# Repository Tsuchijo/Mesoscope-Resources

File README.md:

# TM-Lab-Mesoscope-Resources

## Arduino Code
Installing Arduino IDE:

    Download Arduino IDE:
        Visit the official Arduino website: Arduino Software.
        Choose the appropriate version for your operating system (Windows, macOS, Linux), and download the installer.

    Install Arduino IDE:
        Run the downloaded installer and follow the on-screen instructions.
        On Windows, you might need to install drivers for the Arduino board during the installation process.

    Open Arduino IDE:
        Once installed, open the Arduino IDE.

Installing and Running a Supplied Program:

    Connect Arduino Board:
        Connect your Arduino board to your computer using a USB cable.

    Select Board and Port:
        In the Arduino IDE, go to Tools > Board and select the appropriate Arduino board (e.g., Arduino Uno).
        Also, go to Tools > Port and select the port to which your Arduino board is connected.

    Open a Supplied Program (Sketch):
        Download the sketch from TriggeringstrobingArduinoCode/
        In the Arduino IDE, go to File > open and open the downloaded sketch

    Verify the Sketch:
        Click the checkmark icon (Verify) to check for any errors in the code. Fix any errors if they occur.

    Upload the Sketch:
        Click the right arrow icon (Upload) to compile and upload the sketch to the Arduino board.

## Lens Adapters

All the lens adapters are parametrically created using this onshape file:

https://cad.onshape.com/documents/2f0def30531779d17ee9e510/w/bf5702dd5ef345ce03ccb7df/e/dbd37cfbbbade1fbfb717a2f?renderMode=0&uiState=656536ea70c36e66cdf41a41

Adjust these parameters to change the adapters parameters, the diameter is the inner diameter of the lens, pitch is usually 0.5 or 0.75

## Strobing Trigger

### Circuit Diagrams

### Triggering Unit 

### Routing 

### I/O

For the Master Clock in / power in pin out from left to right is 
- master clock
- ground
- power (5v)

for Timing signal the pinout is
- Brain timing control
- Behavior timing control
- Strobing timing control

with the switches controlling in the same order.

In order to control the width of the timing signal supply a pwm signal to each of the width control signals, with the width corresponding to change in signal. The supplied signal should be greater than 1khz and ideally as high frequency as possible to reduce artifacts

the timing and output pots allow for manual control of timing and output voltage, although each of them can cause errors if pushed to their limits due to variation in their ranges from manufacturing. Never turn the timing pots all the way to the right as that might cause a short

### Using

To use supply a 50hz PWM signal to the master clock with as wide a PWM as possible, the width of the signal corresponding to the maximum possible exposure time.

Supply a 5khz PWM signal for each width control pin in to control the exposure for brain and the behaviour cameras independently. Make sure the switch is switched to ON for the control pin being used. The Width of the PWM signal corresponds with the timing, with the widest signal being the longest exposure time.

Simulation of the circuit can be found at: https://tinyurl.com/ykhpxhtl

### Control Example Code
```import RPi.GPIO as GPIO
import time

# Set GPIO mode and warning
GPIO.setmode(GPIO.BCM)
GPIO.setwarnings(False)

# Define the pin numbers
master_clock_pin = 17
width_control_pin = 18

# Set the frequency for the master clock (50Hz)
master_clock_frequency = 50

# Set the duty cycle for the master clock (99% width)
master_clock_duty_cycle = 99

# Set the frequency for the width control (5kHz)
width_control_frequency = 5000

# Initialize the GPIO pins
GPIO.setup(master_clock_pin, GPIO.OUT)
GPIO.setup(width_control_pin, GPIO.OUT)

# Initialize PWM for master clock
master_clock_pwm = GPIO.PWM(master_clock_pin, master_clock_frequency)
master_clock_pwm.start(master_clock_duty_cycle)

# Function to control the width of the second PWM
def set_width(shutter_speed):
    width_percentage = shutter_speed * 100
    width_control_pwm.ChangeDutyCycle(width_percentage)

# Initialize PWM for width control
width_control_pwm = GPIO.PWM(width_control_pin, width_control_frequency)
width_control_pwm.start(0)  # Start with 0% duty cycle

try:
    # Example: Set shutter speed to 0.5 (50% duty cycle)
    shutter_speed = 0.5
    set_width(shutter_speed)

    # Keep the program running
    while True:
        time.sleep(1)

except KeyboardInterrupt:
    # Clean up on program exit
    master_clock_pwm.stop()
    width_control_pwm.stop()
    GPIO.cleanup()
```

# Throughole Based Triggering System
For making the throughhole 555 trigger there is a .xlsx file with the digikey order needed to create one system. The list can also be found at this link: https://www.digikey.ca/en/mylists/list/3F61W3LRA3. Then the components can be placed on the board based on the silkscreen.

## Circuit Drawing

# Solenoid Driver

The Driver is based on using M7 Mosfet drivers, which max out at ~300 mA of current draw at 12V, anything higher will damage and burn out the driver over time. Not suitable for high power solenoids.

## Circuit Drawing

# Glass Slide Cutting Jigs
https://cad.onshape.com/documents/586ecae177d828403c2f23cb/w/295fcf84d2d2bd0672364755/e/c55ac1745cc839e1a44f1998?renderMode=0&uiState=657b82dfe9d1321263616ee4

the Glass Slide Cutting Jig is parameterized by a variable table which determines the depth of the first and second cuts, made to cut 8mm diameter glass slides, should be 3d printed on fine print settings.

# Columbia Mouse Cup Clear Sides Model
https://cad.onshape.com/documents/b81ce74945475cb4a4585191/w/58aa1f17095117351b4c242d/e/5ae7ff2c3d7fb6816ba1f3a7?renderMode=0&uiState=657b8323ea32e231b383538c

Clear Sided mouse cup for water reaching task. The sides should be laser cut out of 3mm acrylic, the main cup 3d printed.

# Headfix Mount
https://cad.onshape.com/documents/1d2096fc56ebea0ce0825b22/w/af5d367c825ef3549394acac/e/f6e60455f61b46eaad854045?renderMode=0&uiState=657b836199fdb972703cfb45

Model and Drawing for headfix mount, should be tapped and machined. Used JLCPCB to order the Machined versions.

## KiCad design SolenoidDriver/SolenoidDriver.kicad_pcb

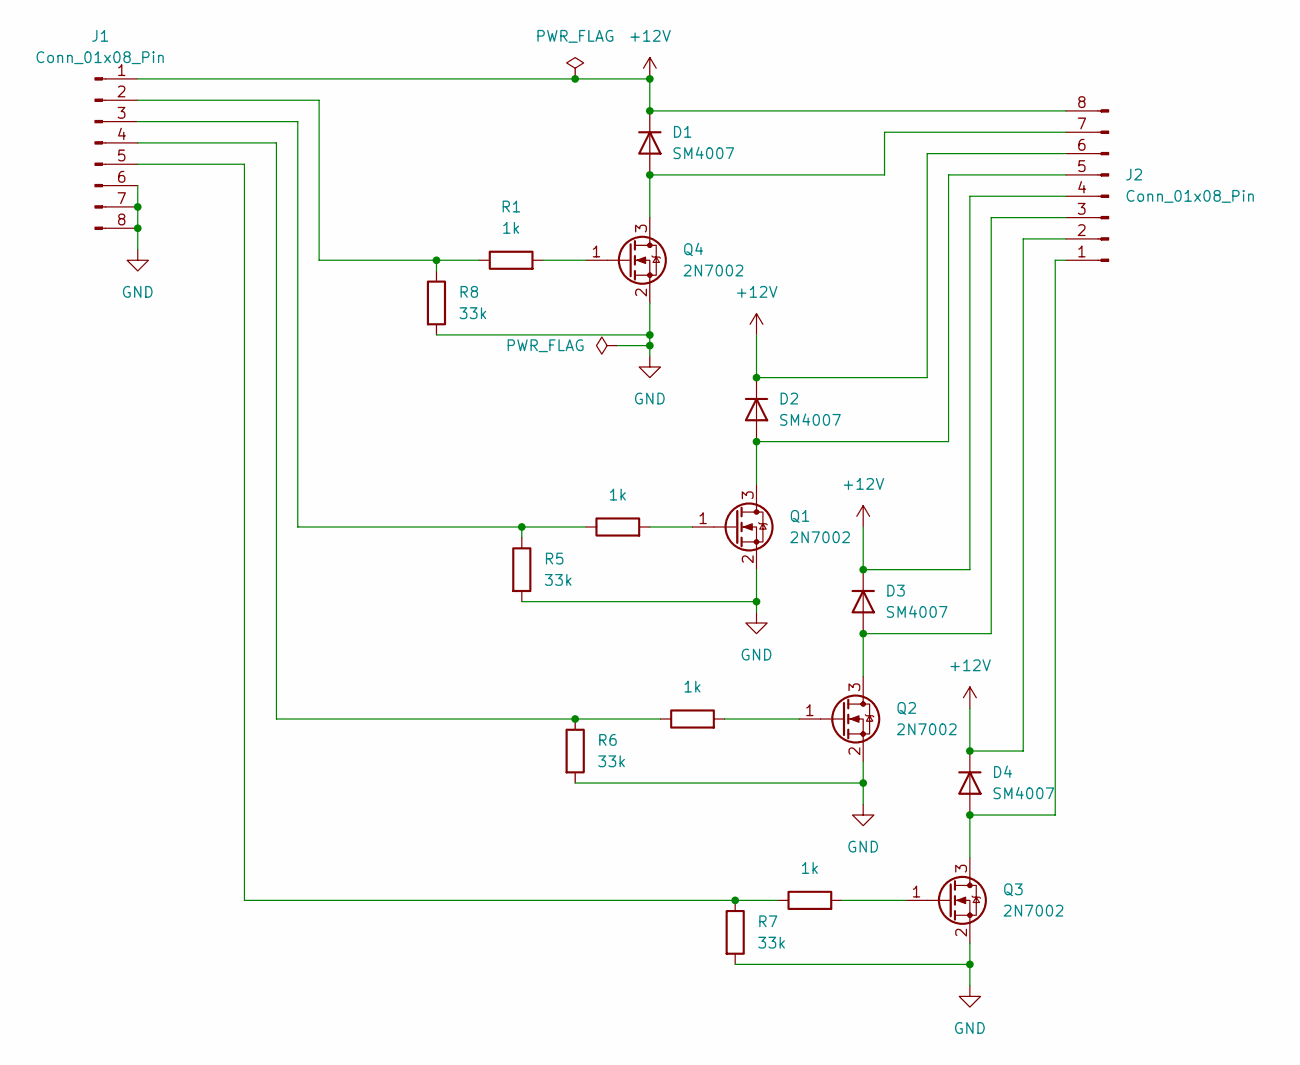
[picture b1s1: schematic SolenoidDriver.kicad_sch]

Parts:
D1, D2, D3, D4: SM4007; D_MELF
J1, J2: Conn_01x08_Pin; PinHeader_1x08_P2.54mm_Vertical
Q1, Q2, Q3, Q4: 2N7002; SOT-23
R1, R2, R3, R4: 1k; R_0603_1608Metric
R5, R6, R7, R8: 33k; R_0603_1608Metric

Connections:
+12V: D1.1 (K), D2.1 (K), D3.1 (K), D4.1 (K), J1.1, J2.2, J2.4, J2.6, J2.8
GND: J1.6, J1.7, J1.8, Q1.2 (S), Q2.2 (S), Q3.2 (S), Q4.2 (S), R5.2, R6.2, R7.2, R8.2
unnamed: D1.2 (A), J2.7, Q4.3 (D)
unnamed: D2.2 (A), J2.5, Q1.3 (D)
unnamed: D3.2 (A), J2.3, Q2.3 (D)
unnamed: D4.2 (A), J2.1, Q3.3 (D)
unnamed: J1.2, R1.1, R8.1
unnamed: J1.3, R2.1, R5.1
unnamed: J1.4, R3.1, R6.1
unnamed: J1.5, R4.1, R7.1
unnamed: Q1.1 (G), R2.2
unnamed: Q2.1 (G), R3.2
unnamed: Q3.1 (G), R4.2
unnamed: Q4.1 (G), R1.2

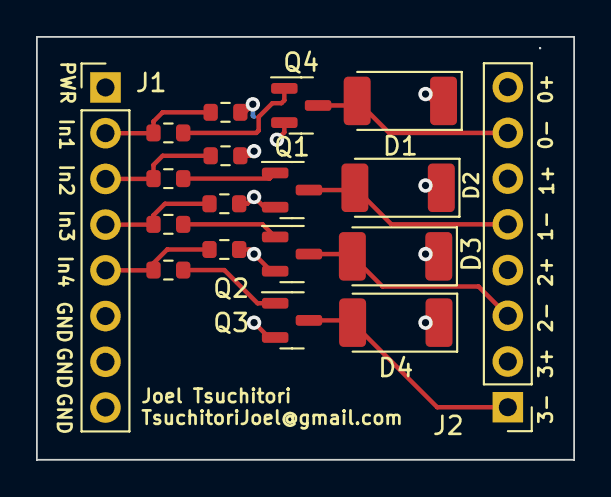
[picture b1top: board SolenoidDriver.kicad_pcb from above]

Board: 2 copper layers, 29.8 x 23.5 mm, 18 parts (0 on the bottom side), 14 nets.

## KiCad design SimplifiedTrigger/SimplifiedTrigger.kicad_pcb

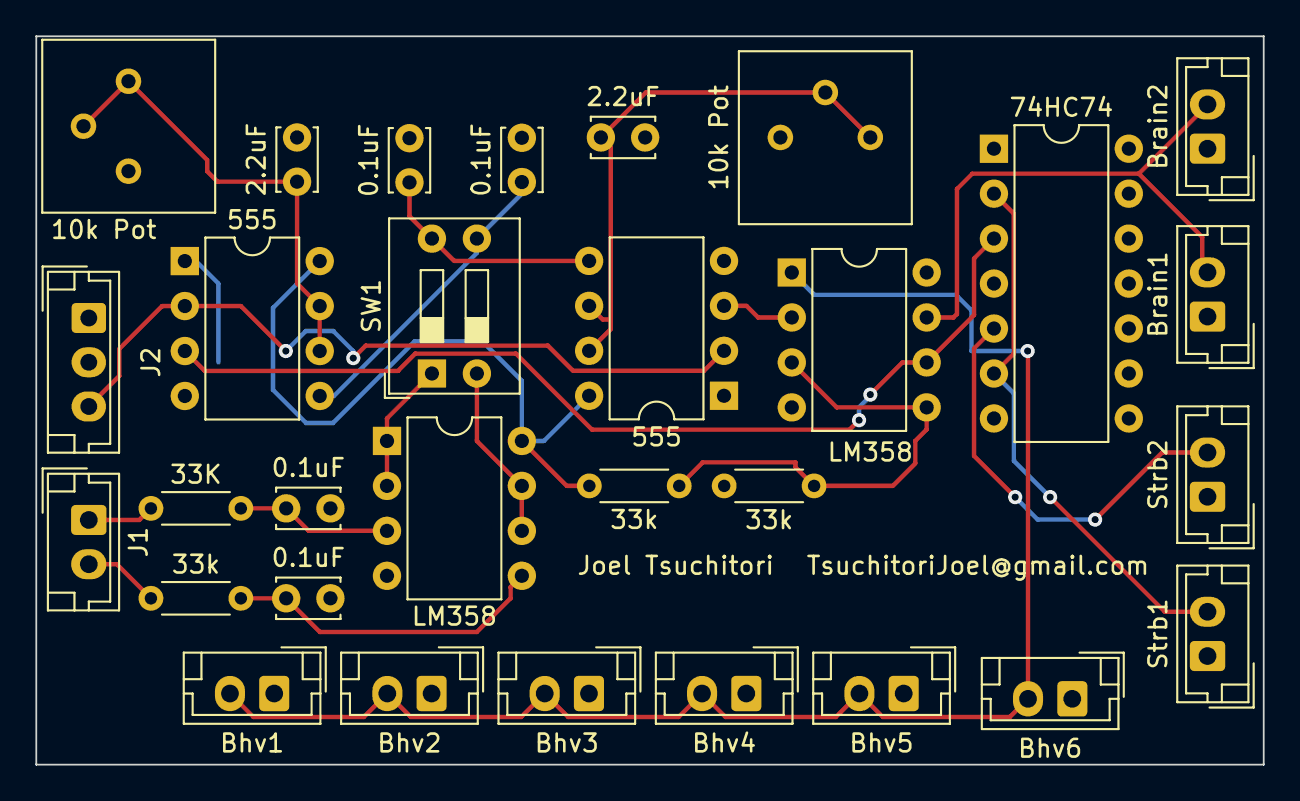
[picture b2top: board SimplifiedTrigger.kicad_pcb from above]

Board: 2 copper layers, 69.3 x 41.1 mm, 30 parts (0 on the bottom side), 20 nets.

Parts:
0.1uF, 0.1uF#2, 0.1uF#3, 0.1uF#4: 0.1 uF; C_Disc_D3.4mm_W2.1mm_P2.50mm
2.2uF, 2.2uF#2: 2.2 uf; C_Disc_D3.4mm_W2.1mm_P2.50mm
10k Pot, 10k Pot#2: 10k-0; Potentiometer_Bourns_3386P_Vertical
33K, 33k, 33k#2, 33k#3: 33k; R_Axial_DIN0204_L3.6mm_D1.6mm_P5.08mm_Horizontal
74HC74: 74HC74; DIP-14_W7.62mm
555, 555#2: NE555P; DIP-8_W7.62mm
Bhv1, Bhv2, Bhv3, Bhv4, Bhv5, Bhv6: Conn_01x02_Pin; JST_EH_B2B-EH-A_1x02_P2.50mm_Vertical
Brain1, Brain2: Conn_01x02_Pin; JST_EH_B2B-EH-A_1x02_P2.50mm_Vertical
J1: Conn_01x02_Pin; JST_EH_B2B-EH-A_1x02_P2.50mm_Vertical
J2: Conn_01x03_Pin; JST_EH_B3B-EH-A_1x03_P2.50mm_Vertical
LM358, LM358#2: LM358; DIP-8_W7.62mm
SW1: SW_DIP_x02; SW_DIP_SPSTx02_Slide_9.78x7.26mm_W7.62mm_P2.54mm
Strb1, Strb2: Conn_01x02_Pin; JST_EH_B2B-EH-A_1x02_P2.50mm_Vertical

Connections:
+5V: 10k Pot.3, 10k Pot#2.3, 33k#2.1, 74HC74.1 (~R), 74HC74.4 (~S), 74HC74.14 (VCC), 555.8 (VCC), 555#2.8 (VCC), J2.1, LM358.8 (V+), LM358#2.8 (V+)
GND: 0.1uF.2, 0.1uF#2.2, 0.1uF#3.2, 0.1uF#4.2, 2.2uF.2, 2.2uF#2.2, 33k#3.2, 74HC74.7 (GND), 555.1 (GND), 555.4 (R), 555#2.1 (GND), 555#2.4 (R), Bhv1.1, Bhv2.1, Bhv3.1, Bhv4.1, Bhv5.1, Bhv6.1, Brain1.1, Brain2.1, J2.2, LM358.4 (V-), LM358#2.4 (V-), Strb1.1, Strb2.1
unnamed: 33K.1, J1.1
unnamed: 33k.1, J1.2
unnamed: Bhv1.2, Bhv2.2, Bhv3.2, Bhv4.2, Bhv5.2, Bhv6.2, LM358#2.1
unnamed: Brain1.2, Brain2.2, LM358#2.7
unnamed: 74HC74.5 (Q), Strb2.2
unnamed: 74HC74.2 (D), 74HC74.6 (~Q), Strb1.2
unnamed: 0.1uF.1, 555.5 (CV), SW1.4
unnamed: 2.2uF#2.1, 10k Pot#2.1, 10k Pot#2.2, 555.6 (THR), 555.7 (DIS)
unnamed: 555.3 (Q), LM358#2.2 (-)
unnamed: 0.1uF#2.1, 33K.2, LM358.3 (+)
unnamed: LM358.1, LM358.2 (-), SW1.1
unnamed: 0.1uF#4.1, 33k.2, LM358.5 (+)
unnamed: LM358.6 (-), LM358.7, SW1.2
unnamed: 0.1uF#3.1, 555#2.5 (CV), SW1.3
unnamed: 2.2uF.1, 10k Pot.1, 10k Pot.2, 555#2.6 (THR), 555#2.7 (DIS)
unnamed: 74HC74.3 (C), 555#2.3 (Q), LM358#2.6 (-)
unnamed: 33k#2.2, 33k#3.1, LM358#2.3 (+), LM358#2.5 (+)
VAC: 555.2 (TR), 555#2.2 (TR), J2.3

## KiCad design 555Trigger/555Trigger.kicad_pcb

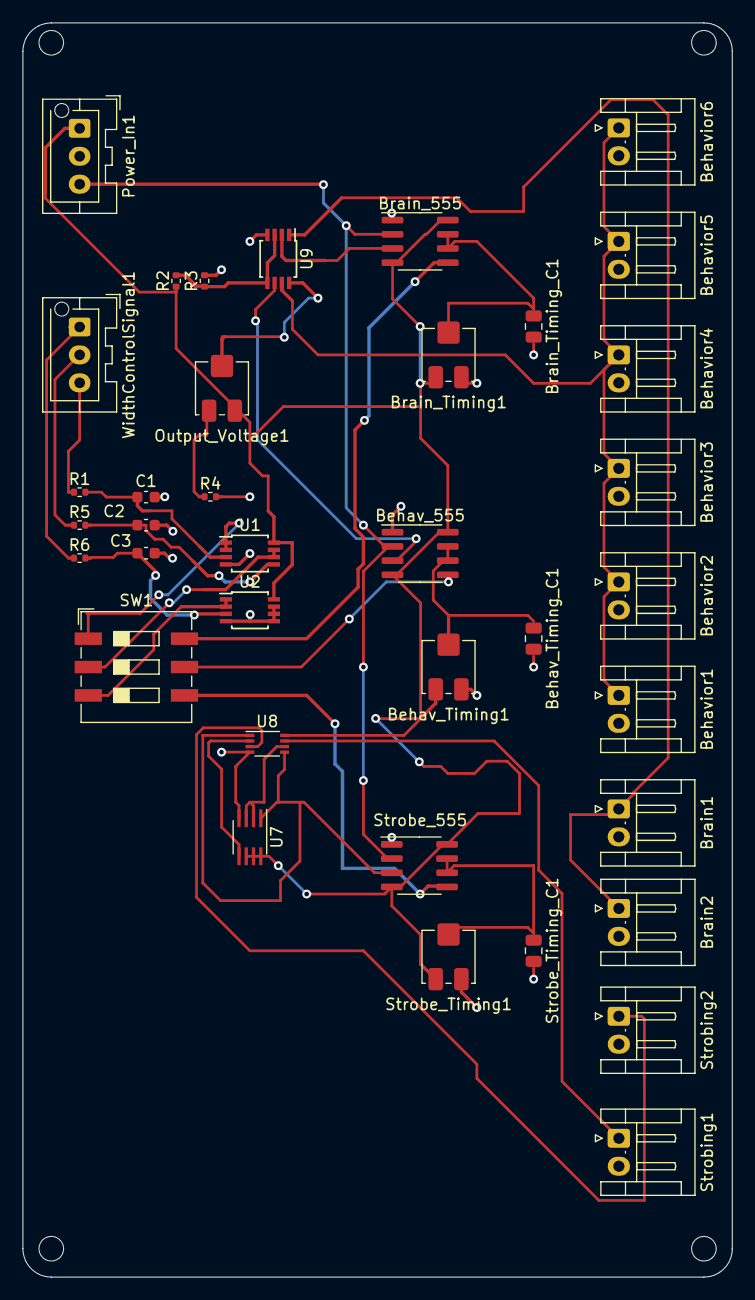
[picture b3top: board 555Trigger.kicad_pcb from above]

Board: 2 copper layers, 63.5 x 112.3 mm, 41 parts (0 on the bottom side), 30 nets.

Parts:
Behav_555: TLC555xD; SOIC-8_3.9x4.9mm_P1.27mm
Behav_Timing1: 0-10k; Potentiometer_Bourns_3314J_Vertical
Behav_Timing_C1: 2.2uF; C_0805_2012Metric
Behavior1, Behavior2, Behavior3, Behavior4, Behavior5, Behavior6: Conn_01x02_Socket; JST_EH_S2B-EH_1x02_P2.50mm_Horizontal
Brain1, Brain2: Conn_01x02_Socket; JST_EH_S2B-EH_1x02_P2.50mm_Horizontal
Brain_555: TLC555xD; SOIC-8_3.9x4.9mm_P1.27mm
Brain_Timing1: 0-10k; Potentiometer_Bourns_3314J_Vertical
Brain_Timing_C1: 2.2uF; C_0805_2012Metric
C1, C2, C3: 10 nF; C_0603_1608Metric
H1, H2, H3, H4: MountingHole; MountingHole_2.2mm_M2
Output_Voltage1: 10k; Potentiometer_Bourns_3314J_Vertical
Power_In1: Conn_01x03_Socket; JST_XA_B03B-XASK-1-A_1x03_P2.50mm_Vertical
R1, R5, R6: 32k; R_0402_1005Metric
R2: 10k; R_0402_1005Metric
R3, R4: 20k; R_0402_1005Metric
SW1: SW_DIP_x03; SW_DIP_SPSTx03_Slide_9.78x9.8mm_W8.61mm_P2.54mm
Strobe_555: TLC555xD; SOIC-8_3.9x4.9mm_P1.27mm
Strobe_Timing1: 0-10k; Potentiometer_Bourns_3314J_Vertical
Strobe_Timing_C1: 2.2uF; C_0805_2012Metric
Strobing1, Strobing2: Conn_01x02_Socket; JST_EH_S2B-EH_1x02_P2.50mm_Horizontal
U1, U2, U9: OPA2333xxD; TSSOP-8_3x3mm_P0.65mm
U7: 74LVC2G74; SSOP-8_2.95x2.8mm_P0.65mm
U8: 74AHC2G00; VSSOP-8_2.3x2mm_P0.5mm
WidthControlSignal1: Conn_01x03_Socket; JST_XA_B03B-XASK-1-A_1x03_P2.50mm_Vertical

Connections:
+5V: Behav_555.4 (R), Behav_555.8 (VCC), Behav_Timing1.3, Brain_555.4 (R), Brain_555.8 (VCC), Brain_Timing1.3, Output_Voltage1.1, Power_In1.1, R2.1, Strobe_555.4 (R), Strobe_555.8 (VCC), Strobe_Timing1.3, U1.8 (V+), U2.8 (V+), U7.6 (~CLR), U7.7 (~PRE), U7.8 (VCC), U8.8 (VCC)
/Behavior_Camera_Unit/CV_In: Behav_555.5 (CV), SW1.5
/Behavior_Camera_Unit/Trigger_Out: Behav_555.3 (Q), U9.6 (-)
/Brain_Camera_Unit/CV_In: Brain_555.5 (CV), SW1.6
/Brain_Camera_Unit/Trigger_Out: Brain_555.3 (Q), U9.2 (-)
/Strobing_Trigger/CV_In: SW1.4, Strobe_555.5 (CV)
/Strobing_Trigger/Trigger_Out: Strobe_555.3 (Q), U7.1 (C), U8.1, U8.5
GND: Behav_555.1 (GND), Behav_Timing1.1, Behav_Timing_C1.2, Behavior1.2, Behavior2.2, Behavior3.2, Behavior4.2, Behavior5.2, Behavior6.2, Brain1.2, Brain2.2, Brain_555.1 (GND), Brain_Timing1.1, Brain_Timing_C1.2, C1.2, C2.2, C3.2, Power_In1.2, R3.2, R4.2, Strobe_555.1 (GND), Strobe_Timing1.1, Strobe_Timing_C1.2, Strobing1.2, Strobing2.2, U1.4 (V-), U2.4 (V-), U2.5 (+), U2.6 (-), U2.7, U7.4 (GND), U8.4 (GND), U9.4 (V-)
unnamed: Behav_555.6 (THR), Behav_555.7 (DIS), Behav_Timing1.2, Behav_Timing_C1.1
unnamed: Behavior1.1, Behavior2.1, Behavior3.1, Behavior4.1, Behavior5.1, Behavior6.1, U9.7
unnamed: Brain1.1, Brain2.1, U9.1
unnamed: Brain_555.6 (THR), Brain_555.7 (DIS), Brain_Timing1.2, Brain_Timing_C1.1
unnamed: Output_Voltage1.3, R4.1
unnamed: Strobe_555.6 (THR), Strobe_555.7 (DIS), Strobe_Timing1.2, Strobe_Timing_C1.1
unnamed: Strobing1.1, U8.7
unnamed: Strobing2.1, U8.3
unnamed: C1.1, R1.2, U1.3 (+)
unnamed: SW1.1, U1.1, U1.2 (-)
unnamed: C2.1, R5.2, U1.5 (+)
unnamed: SW1.2, U1.6 (-), U1.7
unnamed: C3.1, R6.2, U2.3 (+)
unnamed: SW1.3, U2.1, U2.2 (-)
unnamed: U7.2 (D), U7.3 (~Q), U8.6
unnamed: U7.5 (Q), U8.2
unnamed: R2.2, R3.1, U9.3 (+), U9.5 (+)
unnamed: Output_Voltage1.2, U9.8 (V+)
unnamed: R6.1, WidthControlSignal1.1
unnamed: R5.1, WidthControlSignal1.2
unnamed: R1.1, WidthControlSignal1.3
VAC: Behav_555.2 (TR), Brain_555.2 (TR), Power_In1.3, Strobe_555.2 (TR)

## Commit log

2023-09-19 Added Lenses
2023-10-06 Added pcb schematics for pulse extender
2023-10-11 added filtering and buffers to circuit todo: make one large master control board
2023-10-11 Added subsystems for master board
2023-10-13 changed to SMD
2023-10-18 updated timer design
2023-10-19 changed some components to make manufacturing simpler
2023-10-19 changed components to be easier to order
2023-11-29 added more circuit info to readme
2023-11-30 added text description of io
2023-12-04 added earholder and models folder
2023-12-06 added Headfix clamp
2023-12-06 Modified Earfix
2023-12-11 Added manufacturing files for solenoid driver and 555 timer
2023-12-13 updated readme with info on ordering components
2023-12-14 Added info and links to other models
2023-12-18 Added circuit sim to the readme
2023-12-19 added arduinocode
2023-12-19 added guide for using arduino code
